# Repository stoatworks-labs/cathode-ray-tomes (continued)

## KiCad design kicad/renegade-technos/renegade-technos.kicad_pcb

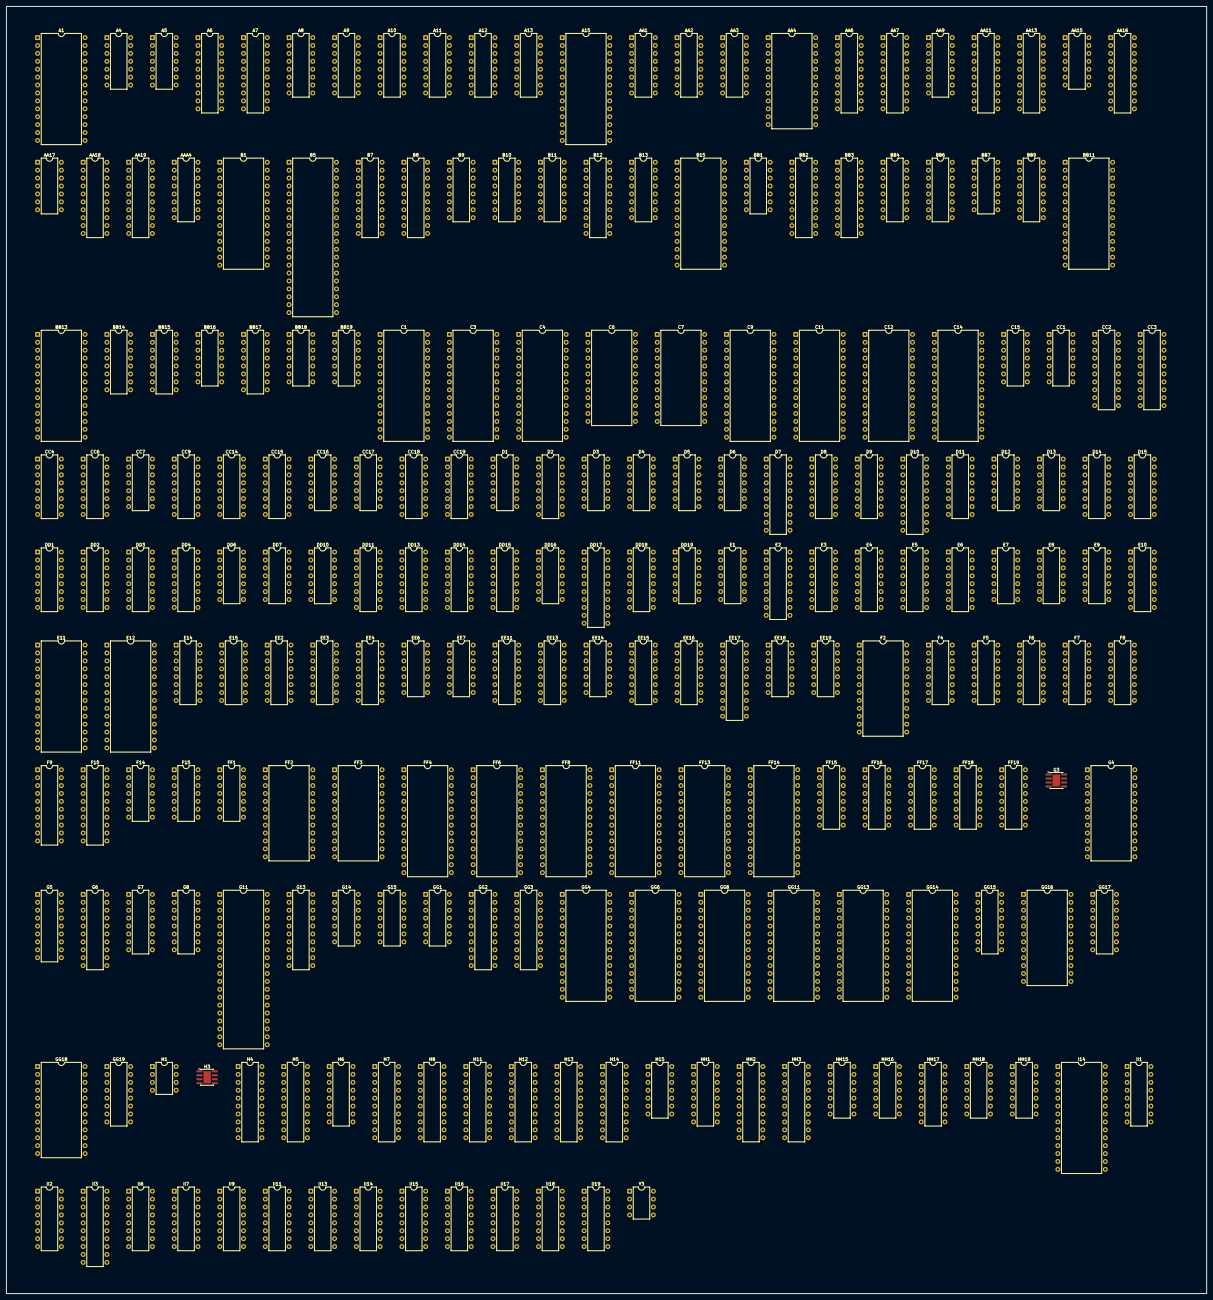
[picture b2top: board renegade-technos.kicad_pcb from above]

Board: 2 copper layers, 385.3 x 413.2 mm, 216 parts (0 on the bottom side), 819 nets, no tracks yet.

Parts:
A1, A15: 27256; DIP-28_W15.24mm
A4: 74LS08; DIP-14_W7.62mm
A5: 74LS00; DIP-14_W7.62mm
A6: 74LS374; DIP-20_W7.62mm
A7: 74LS273; DIP-20_W7.62mm
A8, A9: 74LS174; DIP-16_W7.62mm
A10, A11, A12: 74LS283; DIP-16_W7.62mm
A13: 74LS157; DIP-16_W7.62mm
AA1, AA2, AA3, AA9: 74LS157; DIP-16_W7.62mm
AA4: RAM_2016; DIP-24_W15.24mm
AA6, AA13, AA16: 74LS273; DIP-20_W7.62mm
AA7, AA11: 74LS245; DIP-20_W7.62mm
AA15: 74LS04; DIP-14_W7.62mm
AA17: 74LS86; DIP-14_W7.62mm
AA18, AA19: DIP-20_W7.62mm
AAA4: 74LS138; DIP-16_W7.62mm
B1: HM65256B_SERIES; DIP-28_W15.24mm
B5: MC68A09; DIP-40_W15.24mm
B7, B8: 74LS245; DIP-20_W7.62mm
B9, B10, B11: 74LS157; DIP-16_W7.62mm
B12: 74LS273; DIP-20_W7.62mm
B13: 74LS194; DIP-16_W7.62mm
B15: 27256; DIP-28_W15.24mm
BB1: 74LS10; DIP-14_W7.62mm
BB2, BB3: DIP-20_W7.62mm
BB4, BB6: DIP-16_W7.62mm
BB7: 74LS20; DIP-14_W7.62mm
BB9, BB14: 74LS157; DIP-16_W7.62mm
BB11: HM65256B_SERIES; DIP-28_W15.24mm
BB13: 27256; DIP-28_W15.24mm
BB15, BB17: 74LS163; DIP-16_W7.62mm
BB16, BB18, BB19: 74LS86; DIP-14_W7.62mm
C1, C3, C4, C9, C11, C12, C14: 27256; DIP-28_W15.24mm
C6, C7: RAM_2016; DIP-24_W15.24mm
C15: 74LS04; DIP-14_W7.62mm
CC1: 74LS74; DIP-14_W7.62mm
CC2, CC3: DIP-20_W7.62mm
CC4, CC6, CC14: DIP-16_W7.62mm
CC7: 74LS32; DIP-14_W7.62mm
CC9: 74LS157; DIP-16_W7.62mm
CC15: 74LS163; DIP-16_W7.62mm
CC16: 74LS00; DIP-14_W7.62mm
CC17: 74LS04; DIP-14_W7.62mm
CC18, CC19: 74LS161; DIP-16_W7.62mm
D1, D3: 74LS393; DIP-14_W7.62mm
D2, D15: 74LS157; DIP-16_W7.62mm
D4: 74LS74; DIP-14_W7.62mm
D5: 74LS27; DIP-14_W7.62mm
D6: 74LS04; DIP-14_W7.62mm
D7, D10: 74LS273; DIP-20_W7.62mm
D8, D9: 74LS174; DIP-16_W7.62mm
D11: 74LS139; DIP-16_W7.62mm
D12: 74LS10; DIP-14_W7.62mm
D13: 74LS86; DIP-14_W7.62mm
D14: 74LS194; DIP-16_W7.62mm
DD1: 74LS138; DIP-16_W7.62mm
DD2, DD3: 74LS157; DIP-16_W7.62mm
DD4: 74LS161; DIP-16_W7.62mm
DD6, DD7, DD16: 74LS74; DIP-14_W7.62mm
DD10: 74LS86; DIP-14_W7.62mm
DD11, DD13: 74LS174; DIP-16_W7.62mm
DD14, DD15: DIP-16_W7.62mm
DD17: DIP-20_W7.62mm
DD18: 74LS112; DIP-16_W7.62mm
DD19: 74LS30; DIP-14_W7.62mm
E1, E8: 74LS04; DIP-14_W7.62mm
E2: OKI-M5205; DIP-18_W7.62mm
E3: 74LS174; DIP-16_W7.62mm
E4, E5, E6: 74LS153; DIP-16_W7.62mm
E7: 74LS32; DIP-14_W7.62mm
E9: 74LS20; DIP-14_W7.62mm
E10: 74LS138; DIP-16_W7.62mm
E11, E12: 27256; DIP-28_W15.24mm
E14: 74LS194; DIP-16_W7.62mm
E15: 74LS157; DIP-16_W7.62mm
EE2, EE3, EE15, EE16: 74LS157; DIP-16_W7.62mm
EE4: 74LS161; DIP-16_W7.62mm
EE6: 74LS74; DIP-14_W7.62mm
EE7: 74LS02; DIP-14_W7.62mm
EE11: 74LS138; DIP-16_W7.62mm
EE13: 74LS139; DIP-16_W7.62mm
EE14: 74LS27; DIP-14_W7.62mm
EE17: DIP-20_W7.62mm
EE18: 74LS00; DIP-14_W7.62mm
EE19: 74LS04; DIP-14_W7.62mm
F2: YM3812-3526; DIP-24_W15.24mm
F4, F5, F6, F7: 74LS157; DIP-16_W7.62mm
F8: 74LS174; DIP-16_W7.62mm
F9, F10: 74LS244; DIP-20_W7.62mm
F14: 74LS08; DIP-14_W7.62mm
F15: 74LS14; DIP-14_W7.62mm
FF1: 74LS74; DIP-14_W7.62mm
FF2, FF3: DIP-24_W15.24mm
FF4, FF6, FF8, FF11, FF13, FF14: 27256; DIP-28_W15.24mm
FF15, FF19: 74LS257; DIP-16_W7.62mm
FF16, FF18: 74LS174; DIP-16_W7.62mm
FF17: 74LS157; DIP-16_W7.62mm
G3: L8410-LM358N; SOIC-8-1EP_3.9x4.9mm_P1.27mm_EP2.41x3.81mm
G4: RAM_2016; DIP-24_W15.24mm
G5: NEC_UPD2114; DIP-18_W7.62mm
G6, G13: 74LS245; DIP-20_W7.62mm
G7, G8: 74LS138; DIP-16_W7.62mm
G11: UM6502; DIP-40_W15.24mm
G14, G15: 74LS74; DIP-14_W7.62mm
GG1: 74LS86; DIP-14_W7.62mm
GG2, GG3: DIP-20_W7.62mm
GG4, GG6, GG8, GG11, GG13, GG14: 27256; DIP-28_W15.24mm
GG15, GG19: 74LS257; DIP-16_W7.62mm
GG16, GG18: RAM_2016; DIP-24_W15.24mm
GG17: 74LS157; DIP-16_W7.62mm
H1: MB3730; DIP-8_W7.62mm
H3: M9012-358N; SOIC-8-1EP_3.9x4.9mm_P1.27mm_EP2.41x3.81mm
H4: 74LS245; DIP-20_W7.62mm
H5: 74LS273; DIP-20_W7.62mm
H6: 74LS174; DIP-16_W7.62mm
H7, H8, H11, H12: 74LS244; DIP-20_W7.62mm
H13, H14: 74LS374; DIP-20_W7.62mm
H15: 74LS74; DIP-14_W7.62mm
HH1: 74LS174; DIP-16_W7.62mm
HH2, HH3: DIP-20_W7.62mm
HH15, HH16, HH18, HH19: 74LS86; DIP-14_W7.62mm
HH17: 74LS157; DIP-16_W7.62mm
I14: MC68705P5S; DIP-28_W15.24mm
II1, II2: DIP-16_W7.62mm
II3: DIP-20_W7.62mm
II6, II13, II14, II17: 74LS157; DIP-16_W7.62mm
II7, II9, II11: 74LS194; DIP-16_W7.62mm
II15, II16, II18, II19: 74LS163; DIP-16_W7.62mm
Y3: YM3014; DIP-8_W7.62mm

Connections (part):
/CHPAL0: DD11.7, DD17.17
/CHPAL1: DD11.10, DD17.18
/CHPXL0: D5.4, E4.5, E4.6, EE17.2
/CHPXL1: D5.5, E4.10, E4.11, EE17.5
/CHPXL2: D5.3, E5.5, E5.6, EE17.19
/CHPXL3: DD17.16, E5.10, E5.11
/CHPXL4: DD17.19, E6.5, E6.6
/CHROM0: BB13.11, DD14.3
/CHROM1: BB13.12, DD14.4
/CHROM2: BB13.13, DD14.5
/CHROM3: BB13.15, DD14.6
/CHROM4: BB13.16, CC14.3
/CHROM5: BB13.17, CC14.4
/CN2_C17: II14.6, II14.11
/CNT_VER: DD7.12, EE18.6, EE19.9, G14.3, H8.8
/COUNTER_S0: CC14.9, D15.4, DD14.9
/COUNTER_S1: CC14.10, D15.12, DD14.10
/FLIP_B: AA17.2, AA17.5, AA17.10, AA17.13, BB16.1, BB16.5, BB16.10, BB16.13, BB18.2, BB18.5, BB18.10, BB18.13, BB19.2, BB19.5, BB19.9, BB19.13, D6.10, DD10.2, DD10.13, DD15.1, HH17.3, HH17.14
/H0: AA3.10, AA17.9, BB17.13, D12.3, D15.2, D15.13, DD1.6, EE13.2, F2.24, I14.4
/H1: AA3.6, AA17.12, BB17.12, C15.3, DD1.1, DD6.3, DD7.3, EE13.3
/H2: AA3.13, AA13.11, AA16.11, BB17.11, CC9.10, CC17.13, DD1.2, DD13.9
/H3: AA3.3, BB15.14, BB16.2, CC1.3, CC17.5, DD1.3, E2.16, EE2.14, EE3.13, GG1.1
/H4: AA2.13, BB15.13, BB16.12, CC17.9, DD16.3, EE2.2, EE3.3
/H5: AA2.3, BB15.12, BB16.4, CC16.4, EE2.5, EE3.6
/H6: AA2.6, BB15.11, BB16.9, CC16.12, CC17.11, DD2.14, DD3.13
/H7: AA2.10, CC15.14, CC17.3, DD2.2, DD3.3
/H8: AA1.3, CC1.2, CC15.13, CC16.2, CC16.13, CC17.1, DD2.5, DD3.6, DD6.2, DD10.1, DD16.4, DD18.1, DD18.13
/HBLANKING: EE6.9, EE7.9
/HF2: AA17.1, CC17.12, DD11.9
/HF3: AA16.4, BB16.3
/HF4: AA16.17, BB16.11
/HF5: AA16.3, BB16.6
/HF6: AA16.18, BB16.8
/HF7: AA16.13, AA17.6
/HF8: AA16.7, DD10.11
/HF9: AA16.14, DD10.3
/HF'0: A12.6, AA17.8
/HF'1: A12.2, AA17.11, BB13.7
/HF'2: A12.15, AA17.3, BB13.6
/HF'3: A12.11, AA16.5, BB14.3
/HF'4: A11.6, AA16.16, BB14.6
/HF'5: A11.2, AA16.2, BB14.13
/HF'6: A11.15, AA16.19, BB14.10
/HF'7: A11.11, AA16.12, BB9.10
/HF'8: A10.2, AA16.6
/HF'9: A10.6, AA16.15
/MAIN_AB0: AA3.11, B9.2, BB14.2, F4.2, F9.3, G7.1, G8.1
/MAIN_AB1: AA3.5, B9.5, BB14.14, F4.5, F9.5, G7.2, G8.2
/MAIN_AB2: AA3.14, B9.11, BB14.5, F4.11, F9.7, G7.3, G8.3
/MAIN_AB3: AA3.2, B9.14, BB14.11, F4.14, F9.9
/MAIN_AB4: AA2.14, B10.2, BB9.11, F5.2, F9.18
/MAIN_AB5: AA2.2, B10.5, BB9.5, F5.5, F9.16
/MAIN_AB6: AA2.5, B10.11, BB9.14, F5.11, F9.14
/MAIN_AB7: AA2.11, B10.14, BB9.2, F5.14, F9.12
/MAIN_AB8: AA1.2, B11.2, CC9.2, F6.2, F6.5, F6.11, F6.14, F10.3
/MAIN_AB9: B11.5, CC9.5, F10.5
/MAIN_AB10: B11.11, B11.14, CC9.11, F7.5, F7.11, F10.7
/MAIN_AB11: CC9.14, E10.1, F10.9
/MAIN_AB12: AA9.5, E10.2, F10.12
/MAIN_AB13: E10.3, F10.14
/MAIN_D0: E11.11, E12.11, G11.33, G13.11
/MAIN_D1: E11.12, E12.12, G11.32, G13.12
/MAIN_D2: E11.13, E12.13, G11.31, G13.13
/MAIN_D3: E11.15, E12.15, G11.30, G13.14
/MAIN_D4: E11.16, E12.16, G11.29, G13.15
/MAIN_D5: E11.17, E12.17, G11.28, G13.16
/MAIN_D6: E11.18, E12.18, G11.27, G13.17
/MAIN_D7: E11.19, E12.19, G11.26, G13.18
/MAIN_DB0: A6.13, A7.13, A8.14, AA7.11, AA11.11, B7.18, B8.18, G6.14, G13.9, G15.2, G15.12, H4.18, H7.18, H8.18, H11.18, H12.18, H13.3, H14.2
/MAIN_DB1: A6.14, A7.14, A8.13, AA7.14, AA11.14, B7.17, B8.17, G6.13, G13.8, H4.17, H7.3, H8.3, H11.3, H12.3, H13.18, H14.19
/MAIN_DB2: A6.17, A7.17, AA7.15, AA11.15, B7.16, B8.16, G6.12, G13.7, H4.16, H7.16, H8.16, H11.16, H12.16, H13.4, H14.5
/MAIN_DB3: A6.18, A7.18, AA7.12, AA11.12, B7.15, B8.15, G6.11, G13.6, H4.15, H7.5, H8.5, H11.5, H12.5, H13.17, H14.16
/MAIN_DB4: A6.3, A7.3, AA7.13, AA11.13, B7.14, B8.14, G13.5, H4.14, H7.14, H8.14, H11.14, H12.14, H13.7, H14.6
/MAIN_DB5: A6.4, A7.4, AA7.17, AA11.17, B7.13, B8.13, G13.4, H4.13, H7.7, H8.7, H11.7, H12.7, H13.14, H14.15
/MAIN_DB6: A6.7, A7.7, AA7.16, AA11.16, B7.12, B8.12, G13.3, H4.12, H7.12, H8.12, H11.12, H12.12, H13.8, H14.9
/MAIN_DB7: A6.8, A7.8, AA7.18, AA11.18, B7.11, B8.11, G13.2, H4.11, H7.9, H8.9, H11.9, H12.9, H13.13, H14.12
/MRAM_DB0: AA6.9, CC4.6, CC6.5
/MRAM_DB1: AA6.15, CC4.3, CC6.3
/MRAM_DB2: AA6.5, CC4.13, CC6.14
/MRAM_DB3: AA6.12, CC4.10, CC6.12
/MRAM_DB4: AA6.6, BB4.6, BB6.5
/MRAM_DB5: AA6.2, BB4.3, BB6.3
/MRAM_DB6: AA6.16, BB4.13, BB6.14
/MRAM_DB7: AA6.19, BB4.10, BB6.12
/OBJBUF0: EE17.8, GG17.4
/OBJBUF1: EE17.7, GG17.7
/OBJBUF2: EE17.13, GG17.12
/OBJBUF3: EE17.14, GG17.9
/OBJBUF4: EE17.17, FF17.12
/OBJECT_A0: FF4.10, FF6.10, FF8.10, FF11.10, FF13.10, FF14.10, GG4.10, GG6.10, GG8.10, GG11.10, GG13.10, GG14.10, II3.6
/OBJECT_A1: FF4.9, FF6.9, FF8.9, FF11.9, FF13.9, FF14.9, GG4.9, GG6.9, GG8.9, GG11.9, GG13.9, GG14.9, II3.9
/OBJECT_A2: FF4.8, FF6.8, FF8.8, FF11.8, FF13.8, FF14.8, GG4.8, GG6.8, GG8.8, GG11.8, GG13.8, GG14.8, II3.15
/OBJECT_A3: FF4.7, FF6.7, FF8.7, FF11.7, FF13.7, FF14.7, GG4.7, GG6.7, GG8.7, GG11.7, GG13.7, GG14.7, II3.12
/OBJECT_A4: FF4.6, FF6.6, FF8.6, FF11.6, FF13.6, FF14.6, GG1.6, GG4.6, GG6.6, GG8.6, GG11.6, GG13.6, GG14.6
/OBJECT_A5: FF4.5, FF6.5, FF8.5, FF11.5, FF13.5, FF14.5, GG1.11, GG4.5, GG6.5, GG8.5, GG11.5, GG13.5, GG14.5
/OBJECT_A6: FF4.4, FF6.4, FF8.4, FF11.4, FF13.4, FF14.4, GG4.4, GG6.4, GG8.4, GG11.4, GG13.4, GG14.4, HH3.9
/OBJECT_A7: FF4.3, FF6.3, FF8.3, FF11.3, FF13.3, FF14.3, GG4.3, GG6.3, GG8.3, GG11.3, GG13.3, GG14.3, HH3.5
/OBJECT_A8: FF4.25, FF6.25, FF8.25, FF11.25, FF13.25, FF14.25, GG4.25, GG6.25, GG8.25, GG11.25, GG13.25, GG14.25, HH3.2
/OBJECT_A9: FF4.24, FF6.24, FF8.24, FF11.24, FF13.24, FF14.24, GG4.24, GG6.24, GG8.24, GG11.24, GG13.24, GG14.24, HH3.12
/OBJECT_A10: FF4.21, FF6.21, FF8.21, FF11.21, FF13.21, FF14.21, GG4.21, GG6.21, GG8.21, GG11.21, GG13.21, GG14.21, HH3.19
/OBJECT_A11: FF4.23, FF6.23, FF8.23, FF11.23, FF13.23, FF14.23, GG4.23, GG6.23, GG8.23, GG11.23, GG13.23, GG14.23, HH3.15
/OBJECT_A12: FF4.2, FF6.2, FF8.2, FF11.2, FF13.2, FF14.2, GG4.2, GG6.2, GG8.2, GG11.2, GG13.2, GG14.2, HH3.16
/OBJECT_A13: FF4.26, FF6.26, FF8.26, FF11.26, FF13.26, FF14.26, GG4.26, GG6.26, GG8.26, GG11.26, GG13.26, GG14.26, HH3.6
/OBJPXL0: D5.11, E4.4, EE17.9
/OBJPXL1: D5.9, E4.12, EE17.6
/OBJPXL2: D5.10, E5.4, EE17.12
/OBJPXL3: E5.12, EE17.15
/OBJPXL4: E6.4, EE17.16
/PXLCLK: A9.9, B5.38, B12.11, B13.11, D14.11, E14.11, H5.11, H6.9
/RAM0: F4.4, G4.8, G5.5
/RAM1: F4.7, G4.7, G5.6
/RAM2: F4.9, G4.6, G5.7
/RAM3: F4.12, G4.5, G5.4
/RAM4: F5.4, G4.4, G5.3
/RAM5: F5.7, G4.3, G5.2
/RAM6: F5.9, G4.2, G5.1
/RAM7: F5.12, G4.1, G5.17
/RST_SND: F15.5, F15.8, F15.11
/R_~WB: AA7.1, AA11.1, B7.1, B8.1, E8.3, F10.16, G6.1, G7.6, G8.5, G13.1, H4.1
/SCRPXL0: E4.3, E15.7
/SCRPXL1: E4.13, E15.4
/SCRPXL2: E5.3, E15.12
/SCRPXL3: E5.13, F8.10
/SCRPXL4: E6.3, F8.12
/SCRPXL5: E6.13, F8.15
/SCR_AD0: B7.2, C6.9, D7.3
/SCR_AD1: B7.3, C6.10, D7.4
/SCR_AD2: B7.4, C6.11, D7.7
/SCR_AD3: B7.5, C6.13, D7.8
/SCR_AD4: B7.6, C6.14, D7.13
/SCR_AD5: B7.7, C6.15, D7.14
/SCR_AD6: B7.8, C6.16, D7.17
/SCR_AD7: B7.9, C6.17, D7.18
/SCR_AD8: B8.2, C7.9, D8.3
/SCR_AD9: B8.3, C7.10, D8.4
/SCR_AD10: B8.4, C7.11, D8.6
/SCR_AD11: B8.5, C7.13
/SCR_AD12: B8.6, C7.14
/SCR_AD13: B8.7, C7.15, D8.11
/SCR_AD14: B8.8, C7.16, D8.13
/SCR_AD15: B8.9, C7.17, D8.14
/SND_LATCH_WR: A6.11, D4.3, FF1.12, G8.13
/V0: BB2.1, BB18.9, CC18.14, DD2.1, DD3.1, DD7.2, DD7.11, EE2.1, EE3.1, EE6.2, EE7.5, EE7.6, GG2.1
/V1: BB18.12, CC18.13
/V2: BB18.4, CC18.12
/V3: BB18.1, CC18.11, DD19.12, G14.11
/V4: BB19.10, CC19.14, DD19.4, EE19.1
/V5: BB19.12, CC19.13, DD19.3
/V6: BB19.4, CC19.12, DD19.2
/V7: BB19.1, CC19.11, DD19.1
/VBLANKING: DD7.9, EE7.8
/VF'0: A15.10, AA19.15, B15.10, BB13.10, C9.10, C11.10, C12.10, C14.10
/VF'1: A15.9, AA19.12, B15.9, BB13.9, C9.9, C11.9, C12.9, C14.9
/VF'2: A15.8, AA19.6, B15.8, BB13.8, C9.8, C11.8, C12.8, C14.8
/VF'3: A15.7, AA19.9, B15.7, BB9.6, C9.7, C11.7, C12.7, C14.7
/VF'4: AA19.16, B10.10, BB9.13
/VF'5: AA19.19, B10.13, BB9.3
/VF'6: AA19.5, B11.3, CC9.3
/VF'7: AA19.2, B11.6, CC9.6
/YDIFF0: BB7.13, CC4.2, CC6.1
/YDIFF1: CC4.5, CC6.4
/YDIFF2: BB7.12, CC4.14, CC6.13
/YDIFF3: BB7.9, CC4.11, CC6.10
/YDIFF4: BB4.2, BB6.1
/YDIFF5: BB4.5, BB6.4, CC7.13
/YDIFF6: BB4.14, BB6.13
/YDIFF7: BB4.11, BB6.10
/characters/CODE0: AA13.9, BB13.5
/characters/CODE1: AA13.6, BB13.4
/characters/CODE2: AA13.5, BB13.3
/characters/CODE3: AA13.12, BB13.25
/characters/CODE4: AA13.15, BB13.24
/characters/CODE5: AA13.19, BB13.21
/characters/CODE6: AA13.16, BB13.23
/characters/CODE7: AA13.2, BB13.2
/characters/CODE_Q0: BB13.26, DD13.12
/characters/CODE_Q1: BB13.27, DD13.15
/characters/VRAM_A0: BB11.10, BB14.4
/characters/VRAM_A1: BB11.9, BB14.12
/characters/VRAM_A2: BB11.8, BB14.7
/characters/VRAM_A3: BB11.7, BB14.9
/characters/VRAM_A4: BB9.9, BB11.6
/characters/VRAM_A5: BB9.7, BB11.5
/characters/VRAM_A6: BB9.12, BB11.4
/characters/VRAM_A7: BB9.4, BB11.3
/characters/VRAM_A8: BB11.25, CC9.4
/characters/VRAM_A9: BB11.24, CC9.7
/characters/VRAM_A10: BB11.21, CC9.9
/characters/VRAM_A11: BB11.23, CC9.12
/characters/VRAM_A12: AA9.7, BB11.2
/characters/VRAM_D0: AA11.9, AA13.8, BB11.11, DD11.4
/characters/VRAM_D1: AA11.6, AA13.7, BB11.12, DD11.3
/characters/VRAM_D2: AA11.5, AA13.4, BB11.13
/characters/VRAM_D3: AA11.8, AA13.13, BB11.15
/characters/VRAM_D4: AA11.7, AA13.14, BB11.16
/characters/VRAM_D5: AA11.3, AA13.18, BB11.17
/characters/VRAM_D6: AA11.4, AA13.17, BB11.18, DD11.14
/characters/VRAM_D7: AA11.2, AA13.3, BB11.19, DD11.13
/characters/VRAM_Q0: DD11.5, DD13.13
/characters/VRAM_Q1: DD11.2, DD13.14
/characters/~WE_CHAR: AA9.9, BB11.27
/colmix/BLUE_CE: E8.5, F6.12
/colmix/RAM_AD0: G5.14, G6.6, H6.6
/colmix/RAM_AD1: G5.13, G6.7, H6.4
/colmix/RAM_AD2: G5.12, G6.8, H6.3
/colmix/RAM_AD3: G5.11, G6.9, H6.11
/colmix/RAM_D0: G4.9, H4.2, H5.3
/colmix/RAM_D1: G4.10, H4.3, H5.4
/colmix/RAM_D2: G4.11, H4.4, H5.7
/colmix/RAM_D3: G4.13, H4.5, H5.8
/colmix/RAM_D4: G4.14, H4.6, H5.13
/colmix/RAM_D5: G4.15, H4.7, H5.14
/colmix/RAM_D6: G4.16, H4.8, H5.17
/colmix/RAM_D7: G4.17, H4.9, H5.18
/colmix/RAM_~CS: F6.4, G4.18
/colmix/S0: D5.8, E4.14, E5.14, E6.14, F5.10
/colmix/S1: D5.6, E4.2, E5.2, E6.2, F5.13
/colmix/TLS_MTPX0: E4.7, F4.3
/colmix/TLS_MTPX1: E4.9, F4.6
/colmix/TLS_MTPX2: E5.7, F4.13
/colmix/TLS_MTPX3: E5.9, F4.10
/colmix/TLS_MTPX4: E6.7, F5.3
/colmix/TLS_MTPX5: E6.9, F5.6
/colmix/~RG_CE: F6.7, H4.19
/main/BANK: E11.27, G15.9
/main/BANK_ROM: D11.11, E11.20
/main/BANK_SEL: G8.10, G15.11
/main/CLK_Ø2: F10.2, G11.39
/main/CLKØ2_B: D12.4, E10.6, F10.18
/main/MAIN2MCU: G8.11, H13.11, H15.10
/main/MAIN_A0: E11.10, E12.10, F9.17, G11.9
/main/MAIN_A1: E11.9, E12.9, F9.15, G11.10
/main/MAIN_A2: E11.8, E12.8, F9.13, G11.11
/main/MAIN_A3: E11.7, E12.7, F9.11, G11.12
/main/MAIN_A4: E11.6, E12.6, F9.2, G11.13
/main/MAIN_A5: E11.5, E12.5, F9.4, G11.14
/main/MAIN_A6: E11.4, E12.4, F9.6, G11.15
/main/MAIN_A7: E11.3, E12.3, F9.8, G11.16
/main/MAIN_A8: E11.25, E12.25, F10.17, G11.17
/main/MAIN_A9: E11.24, E12.24, F10.15, G11.18
/main/MAIN_A10: E11.21, E12.21, F10.13, G11.19
/main/MAIN_A11: E11.23, E12.23, F10.11, G11.20
/main/MAIN_A12: E11.2, E12.2, F10.8, G11.22
/main/MAIN_A13: E11.26, E12.26, F10.6, G11.23
/main/MAIN_A14: D11.14, E10.4, E12.27, G11.24
/main/MAIN_A15: D11.13, E8.9, E10.5, G11.25
/main/MCU_INT: H15.9, I14.8
/main/PA0: H13.2, H14.3, I14.20
/main/PA1: H13.19, H14.18, I14.21
/main/PA2: H13.5, H14.4, I14.22
/main/PA3: H13.16, H14.17, I14.23
/main/PA4: H13.6, H14.7, I14.24
/main/PA5: H13.15, H14.14, I14.25
/main/PA6: H13.9, H14.8, I14.26
/main/PA7: H13.12, H14.13, I14.27
/main/R_~W: F10.4, G11.34
/main/R_~WMAIN: D12.5, E8.4, E11.22, E12.22
/main/~IRQ: G11.4, G14.8
/main/~LATCHES: E10.7, G7.4, G7.5, G8.4
/main/~MCU2MAIN: F14.13, G7.11, H14.1
/main/~MCUCLR: F14.12, G7.10, H15.13
/main/~MCU_RD: H13.1, H15.11, I14.13
/main/~MCU_WR: H14.11, H15.3, I14.14
/objects/BANK0: EE11.1, FF4.27, FF6.27, GG4.27, GG6.27, II3.16
/objects/BANK1: EE11.2, EE13.14, II3.19
/objects/BANK2: EE11.3, EE13.13, GG1.4, II3.5
/objects/CLK_H: DD4.1, EE4.1, EE18.11
/objects/CLK_H8: BB1.9, CC1.9, EE6.12
/objects/CV: AA16.1, CC19.15, DD18.2, DD18.3, EE2.11, EE3.10, EE19.13, GG1.2
/objects/H8_Q: CC1.5, CC1.12
/objects/HFLIP: FF1.9, GG1.5, GG1.12, GG15.11, GG19.11, HH1.14
/objects/HFLIP': HH1.15, II13.1, II14.1
/objects/LINE: EE6.5, EE15.1, EE16.1, FF17.1, GG17.1, HH17.1
/objects/LUTA_A0: EE2.9, FF2.8
/objects/LUTA_A1: EE2.12, FF2.7
/objects/LUTA_A2: EE2.4, FF2.6
/objects/LUTA_A3: EE2.7, FF2.5
/objects/LUTA_A4: DD2.12, FF2.4
/objects/LUTA_A5: DD2.4, FF2.3
/objects/LUTA_A6: DD2.7, FF2.2
/objects/LUTA_B0: EE3.9, FF3.8
/objects/LUTA_B1: EE3.12, FF3.7
/objects/LUTA_B2: EE3.4, FF3.6
/objects/LUTA_B3: EE3.7, FF3.5
/objects/LUTA_B4: DD3.12, FF3.4
/objects/LUTA_B5: DD3.4, FF3.3
/objects/LUTA_B6: DD3.7, FF3.2
/objects/OBJIN0: EE14.3, EE15.3, EE16.2, II13.4
/objects/OBJIN1: EE14.5, EE15.10, EE16.11, II13.7
/objects/OBJIN2: EE14.4, EE15.13, EE16.14, II13.12
/objects/OBJPAL3: HH1.3, HH2.19
/objects/OBJPAL4: HH1.4, HH2.15
/objects/PXL_CLK: AA15.3, AA15.5, BB17.14, CC2.11, CC3.11, DD6.11, EE18.10, FF16.9, FF18.9
/objects/RAM_AQ0: GG2.6, GG3.6, HH2.7, II1.2, II2.13, II16.3, II19.3
/objects/RAM_AQ1: GG2.5, GG3.5, HH2.4, HH3.4, II2.6, II16.4, II19.4
/objects/RAM_AQ2: GG2.2, GG3.2, HH2.3, HH3.3, II2.4, II16.5, II19.5
/objects/RAM_AQ3: GG2.19, GG3.19, HH2.8, HH3.13, II2.11, II16.6, II19.6
/objects/RAM_AQ4: GG2.16, GG3.16, HH2.18, HH3.18, II2.14, II15.3, II18.3
/objects/RAM_AQ5: GG2.15, GG3.15, HH2.14, HH3.14, II15.4, II18.4
/objects/RAM_AQ6: GG2.12, GG3.12, HH2.17, HH3.17, II15.5, II18.5
/objects/RAM_AQ7: GG2.9, GG3.9, HH2.13, HH3.7, II15.6, II18.6
/objects/SEL_SPRT0: FF8.27, FF11.27, FF13.27, FF14.27, GG8.27, GG11.27, GG13.27, GG14.27, II3.2, II6.1
/objects/VHQ: DD7.5, II17.1
/objects/YAUX: BB7.10, CC7.11
/objects/counters/CLK_XTAL: AA15.10, BB15.2, BB17.2, CC15.2
/objects/counters/HLC: BB15.7, BB15.10, BB17.15, CC15.7
/objects/counters/HUC: BB15.15, CC15.10, CC16.1
/objects/counters/TCV: CC18.15, CC19.7, CC19.10
/objects/counters/V8: DD18.5, DD18.11, EE18.1
/objects/counters/~OBJST3: EE13.7, EE19.5
/objects/counters/~PE: CC18.9, CC19.9, EE19.12
/objects/double_line_buffer.sch/1: EE16.7, FF19.1, GG19.1
/objects/double_line_buffer.sch/2: EE16.4, FF19.5
/objects/double_line_buffer.sch/3: EE16.12, FF19.11
/objects/double_line_buffer.sch/BLANK: EE14.6, EE15.6, EE16.5
/objects/double_line_buffer.sch/BLANK': EE15.7, FF15.1, GG15.1
/objects/double_line_buffer.sch/BUFIN0: EE15.4, FF15.5
/objects/double_line_buffer.sch/BUFIN1: EE15.9, FF15.14
/objects/double_line_buffer.sch/BUFIN2: EE15.12, FF15.11
/objects/double_line_buffer.sch/BUFIN3: FF15.2, FF19.14, HH1.2
/objects/double_line_buffer.sch/BUFIN4: GG15.2, HH1.5
/objects/double_line_buffer.sch/LINEA0: FF18.6, FF19.7, GG18.9
/objects/double_line_buffer.sch/LINEA1: FF18.4, FF19.4, GG18.10
/objects/double_line_buffer.sch/LINEA2: FF18.3, FF19.9, GG18.11
/objects/double_line_buffer.sch/LINEA3: FF18.13, FF19.12, GG18.13
/objects/double_line_buffer.sch/LINEA4: FF18.11, GG18.14, GG19.9
/objects/double_line_buffer.sch/LINEB0: FF15.7, FF16.3, GG16.9
/objects/double_line_buffer.sch/LINEB1: FF15.12, FF16.4, GG16.10
/objects/double_line_buffer.sch/LINEB2: FF15.9, FF16.6, GG16.11
/objects/double_line_buffer.sch/LINEB3: FF15.4, FF16.13, GG16.13
/objects/double_line_buffer.sch/LINEB4: FF16.11, GG15.9, GG16.14
/objects/double_line_buffer.sch/~MR_A: II17.4, II18.1, II19.1
/objects/double_line_buffer.sch/~MR_B: II15.1, II16.1, II17.12
/objects/double_line_buffer.sch/~PE_LINEA: II17.7, II18.9, II19.9
/objects/double_line_buffer.sch/~PE_LINEB: II15.9, II16.9, II17.9
/objects/obj_draw/OBJECT_D0: FF4.11, FF6.11, GG4.11, GG6.11, II6.11
/objects/obj_draw/OBJECT_D1: FF4.12, FF6.12, GG4.12, GG6.12, II6.2
/objects/obj_draw/OBJECT_D2: FF4.13, FF6.13, GG4.13, GG6.13, II6.14
/objects/obj_draw/OBJECT_D3: FF4.15, FF6.15, GG4.15, GG6.15, II6.5
/objects/obj_draw/OBJECT_D4: FF4.16, FF6.16, GG4.16, GG6.16, II6.10
/objects/obj_draw/OBJECT_D5: FF4.17, FF6.17, GG4.17, GG6.17, II6.3
/objects/obj_draw/OBJECT_D6: FF4.18, FF6.18, GG4.18, GG6.18, II6.13
/objects/obj_draw/OBJECT_D7: FF4.19, FF6.19, GG4.19, GG6.19, II6.6
/objects/obj_draw/OBJ_D0: FF8.11, FF11.11, FF13.11, FF14.11, GG8.11, GG11.11, GG13.11, GG14.11, II11.3
/objects/obj_draw/OBJ_D1: FF8.12, FF11.12, FF13.12, FF14.12, GG8.12, GG11.12, GG13.12, GG14.12, II11.4
/objects/obj_draw/OBJ_D2: FF8.13, FF11.13, FF13.13, FF14.13, GG8.13, GG11.13, GG13.13, GG14.13, II11.5
/objects/obj_draw/OBJ_D3: FF8.15, FF11.15, FF13.15, FF14.15, GG8.15, GG11.15, GG13.15, GG14.15, II11.6
/objects/obj_draw/OBJ_D4: FF8.16, FF11.16, FF13.16, FF14.16, GG8.16, GG11.16, GG13.16, GG14.16, II9.3
/objects/obj_draw/OBJ_D5: FF8.17, FF11.17, FF13.17, FF14.17, GG8.17, GG11.17, GG13.17, GG14.17, II9.4
/objects/obj_draw/OBJ_D6: FF8.18, FF11.18, FF13.18, FF14.18, GG8.18, GG11.18, GG13.18, GG14.18, II9.5
/objects/obj_draw/OBJ_D7: FF8.19, FF11.19, FF13.19, FF14.19, GG8.19, GG11.19, GG13.19, GG14.19, II9.6
/objects/obj_draw/SR0: II7.9, II9.9, II11.9, II14.9
/objects/obj_draw/SR1: II7.10, II9.10, II11.10, II14.7
/objects/obj_draw/memories_sprite.sch/~GFXA0: EE13.12, FF6.20
/objects/obj_draw/memories_sprite.sch/~GFXA1: EE11.15, FF14.20
/objects/obj_draw/memories_sprite.sch/~GFXA2: EE11.14, GG14.20
/objects/obj_draw/memories_sprite.sch/~GFXB0: EE13.11, GG6.20
/objects/obj_draw/memories_sprite.sch/~GFXB1: EE11.13, FF13.20
/objects/obj_draw/memories_sprite.sch/~GFXB2: EE11.12, GG13.20
/objects/obj_draw/memories_sprite.sch/~GFXC0: EE13.10, FF4.20
/objects/obj_draw/memories_sprite.sch/~GFXC1: EE11.11, FF11.20
/objects/obj_draw/memories_sprite.sch/~GFXC2: EE11.10, GG11.20
/objects/obj_draw/memories_sprite.sch/~GFXD0: EE13.9, GG4.20
/objects/obj_draw/memories_sprite.sch/~GFXD1: EE11.9, FF8.20
/objects/obj_draw/memories_sprite.sch/~GFXD2: EE11.7, GG8.20
/objects/obj_lut_buf/A0: AA3.9, AA4.8
/objects/obj_lut_buf/A1: AA3.7, AA4.7
/objects/obj_lut_buf/A2: AA3.12, AA4.6
/objects/obj_lut_buf/A3: AA3.4, AA4.5
/objects/obj_lut_buf/A4: AA2.12, AA4.4
/objects/obj_lut_buf/A5: AA2.4, AA4.3
/objects/obj_lut_buf/A6: AA2.7, AA4.2
/objects/obj_lut_buf/A7: AA2.9, AA4.1
/objects/obj_lut_buf/A8: AA1.4, AA4.23
/objects/obj_lut_buf/D0: AA4.9, AA6.8, AA7.9
/objects/obj_lut_buf/D1: AA4.10, AA6.14, AA7.6
/objects/obj_lut_buf/D2: AA4.11, AA6.4, AA7.5
/objects/obj_lut_buf/D3: AA4.13, AA6.13, AA7.8
/objects/obj_lut_buf/D4: AA4.14, AA6.7, AA7.7
/objects/obj_lut_buf/D5: AA4.15, AA6.3, AA7.3
/objects/obj_lut_buf/D6: AA4.16, AA6.17, AA7.4
/objects/obj_lut_buf/D7: AA4.17, AA6.18, AA7.2, CC7.12
/objects/obj_lut_buf/GFX_A0: BB2.8, BB3.8, CC4.7
/objects/obj_lut_buf/GFX_A1: BB2.7, BB3.7, CC4.4
/objects/obj_lut_buf/GFX_A2: BB2.4, BB3.4, CC4.12
/objects/obj_lut_buf/GFX_A3: BB2.3, BB3.3, CC4.9
/objects/obj_lut_buf/GFX_A4: BB2.13, BB3.13, BB4.7
/objects/obj_lut_buf/GFX_A5: BB2.14, BB3.14, BB4.4
/objects/obj_lut_buf/GFX_A6: BB2.17, BB3.17, BB4.12
/objects/obj_lut_buf/GFX_A7: BB2.18, BB3.18, BB4.9
/objects/obj_lut_buf/Q0: HH2.6, II3.3
/objects/obj_lut_buf/Q1: HH2.5, II3.17
/objects/obj_lut_buf/Q2: HH2.2, II3.18
/objects/obj_lut_buf/Q3: HH2.9, II3.4
/objects/obj_lut_buf/Q7: HH2.12, II1.1
/objects/obj_lut_buf/RAM_A0: CC2.2, FF2.9, GG2.7
/objects/obj_lut_buf/RAM_A1: CC2.5, FF2.10, GG2.4
/objects/obj_lut_buf/RAM_A2: CC2.6, FF2.11, GG2.3
/objects/obj_lut_buf/RAM_A3: CC2.9, FF2.13, GG2.18
/objects/obj_lut_buf/RAM_A4: CC2.19, FF2.14, GG2.17
/objects/obj_lut_buf/RAM_A5: CC2.16, FF2.15, GG2.14
/objects/obj_lut_buf/RAM_A6: CC2.15, FF2.16, GG2.13
/objects/obj_lut_buf/RAM_A7: CC2.12, FF2.17, GG2.8
/objects/obj_lut_buf/RAM_B0: CC3.2, FF3.9, GG3.7
/objects/obj_lut_buf/RAM_B1: CC3.5, FF3.10, GG3.4
/objects/obj_lut_buf/RAM_B2: CC3.6, FF3.11, GG3.3
/objects/obj_lut_buf/RAM_B3: CC3.9, FF3.13, GG3.18
/objects/obj_lut_buf/RAM_B4: CC3.19, FF3.14, GG3.17
/objects/obj_lut_buf/RAM_B5: CC3.16, FF3.15, GG3.14
/objects/obj_lut_buf/RAM_B6: CC3.15, FF3.16, GG3.13
/objects/obj_lut_buf/RAM_B7: CC3.12, FF3.17, GG3.8
/objects/obj_lut_buf/RAM_QM0: HH3.8, II1.4
/objects/obj_lut_buf/ROBJ_A'0: II2.12, II3.7
/objects/obj_lut_buf/ROBJ_A'1: II2.7, II3.8
/objects/obj_lut_buf/ROBJ_A'2: II2.5, II3.14
/objects/obj_lut_buf/ROBJ_A'3: II2.10, II3.13
/objects/obj_lut_buf/ROBJ_A'4: II1.3, II2.15
/objects/obj_lut_buf/VF0: AA18.14, BB18.8, CC6.6
/objects/obj_lut_buf/VF1: AA18.13, BB18.11, CC6.2
/objects/obj_lut_buf/VF2: AA18.7, BB18.6, CC6.15
/objects/obj_lut_buf/VF3: AA18.8, BB18.3, CC6.11
/objects/obj_lut_buf/VF4: AA18.17, BB6.6, BB19.8
/objects/obj_lut_buf/VF5: AA18.18, BB6.2, BB19.11
/objects/obj_lut_buf/VF6: AA18.4, BB6.15, BB19.6
/objects/obj_lut_buf/VF7: AA18.3, BB6.11, BB19.3
/objects/obj_lut_buf/~V0: BB3.1, EE7.4, GG3.1
/objects/obj_lut_buf/~WE: AA1.12, AA4.21
/objects/~B1: DD1.14, II2.9
/objects/~B3: DD1.12, HH2.11
/objects/~B5: DD1.10, FF1.11, HH3.11, II3.11
/objects/~B7: DD1.7, EE19.3, HH1.9, II17.5, II17.10
/objects/~CLK_CNTER: AA18.11, AA19.11, CC17.2, CC18.2, CC19.2
/objects/~CLK_H: CC1.11, CC17.6, EE6.3
/objects/~H8_Q: BB1.10, CC1.6
/objects/~MATCH: DD2.10, DD3.11, DD4.2, EE4.2, EE18.8
/objects/~OBJST1: BB4.1, CC4.1, EE13.5, FF1.3, GG2.11, GG3.11
/objects/~OBJST2: DD2.11, DD3.10, EE13.6
/objects/~WE_LUTA: CC2.1, DD2.9, FF2.21
/objects/~WE_LUTB: CC3.1, DD3.9, FF3.21
/scroll/CARRY0: A9.15, B10.6
/scroll/CLK_SCOLM: C15.11, D13.11, F8.9
/scroll/REPAIR: A9.12, B10.3
/scroll/SCOL0: D9.2, F8.14
/scroll/SCOL1: D9.5, F8.13
/scroll/SCOL2: D9.7, F8.11
/scroll/SCR0: D7.2, D10.18
/scroll/SCR1: D7.5, D10.17
/scroll/SCR2: D7.6, D10.14
/scroll/SCR3: D7.9, D10.13
/scroll/SCR4: D7.12, D10.8
/scroll/SCR5: D7.15, D10.7
/scroll/SCR6: D7.16, D10.4
/scroll/SCR7: D7.19, D10.3
/scroll/SCR8: D8.2, D9.14
/scroll/SCR9: D8.5, D9.13
/scroll/SCR10: D8.7, D9.11
/scroll/SCR13: D8.10, D9.6
/scroll/SCR14: D8.12, D9.4
/scroll/SCR15: D8.15, D9.3
/scroll/SCROM_A4: A15.6, B12.12, B15.6, C9.6, C11.6, C12.6, C14.6, D13.12
/scroll/SCROM_A5: A15.5, B15.5, C9.5, C11.5, C12.5, C14.5, C15.12
/scroll/SCROM_A6: A15.4, B15.4, C9.4, C11.4, C12.4, C14.4, D10.19
/scroll/SCROM_A7: A15.3, B15.3, C9.3, C11.3, C12.3, C14.3, D10.16
/scroll/SCROM_A8: A15.25, B15.25, C9.25, C11.25, C12.25, C14.25, D10.15
/scroll/SCROM_A9: A15.24, B15.24, C9.24, C11.24, C12.24, C14.24, D10.12
/scroll/SCROM_A10: A15.21, B15.21, C9.21, C11.21, C12.21, C14.21, D10.9
/scroll/SCROM_A11: A15.23, B15.23, C9.23, C11.23, C12.23, C14.23, D10.6
/scroll/SCROM_A12: A15.2, B15.2, C9.2, C11.2, C12.2, C14.2, D10.5
/scroll/SCROM_A13: A15.26, B15.26, C9.26, C11.26, C12.26, C14.26, D10.2
/scroll/SCROM_A14: A15.27, B15.27, D9.12, D11.2
/scroll/SCROM_A15: A13.1, C9.27, C11.27, C12.27, C14.27, D9.15
/scroll/SCRPOS0: A7.12, A12.5
/scroll/SCRPOS1: A7.15, A12.3
/scroll/SCRPOS2: A7.16, A12.14
/scroll/SCRPOS3: A7.19, A12.12
/scroll/SCRPOS4: A7.2, A11.5
/scroll/SCRPOS5: A7.5, A11.3
/scroll/SCRPOS6: A7.6, A11.14
/scroll/SCRPOS7: A7.9, A11.12
/scroll/SCRPOS8: A8.15, A10.5
/scroll/SCRPOS9: A8.12, A10.3
/scroll/SCR_A0: B9.4, C6.8, C7.8
/scroll/SCR_A1: B9.7, C6.7, C7.7
/scroll/SCR_A2: B9.9, C6.6, C7.6
/scroll/SCR_A3: B9.12, C6.5, C7.5
/scroll/SCR_A4: B10.4, C6.4, C7.4
/scroll/SCR_A5: B10.7, C6.3, C7.3
/scroll/SCR_A6: B10.9, C6.2, C7.2
/scroll/SCR_A7: B10.12, C6.1, C7.1
/scroll/SCR_A8: B11.4, C6.23, C7.23
/scroll/SCR_A9: B11.7, C6.22, C7.22
/scroll/SCR_CA0: B9.3, B12.2
/scroll/SCR_CA1: B9.10, B12.5
/scroll/SCR_CA2: B9.13, B12.6
/scroll/SCR_CA3: B9.6, B12.9
/scroll/SCR_CA5: B12.15, C15.13
/scroll/SCR_CA6: B12.16, D13.4
/scroll/SCR_CA7: B12.19, D13.1
/scroll/SD0: A11.4, B12.3
/scroll/SD1: A11.10, B12.4
/scroll/SD2: A11.1, B12.7
/scroll/SD3: A11.13, B12.8
/scroll/SD4: A12.13, B12.13
/scroll/SD5: A12.10, B12.14
/scroll/SD6: A12.1, B12.17
/scroll/SD7: A12.4, B12.18
/scroll/scrom_memories/FLIP: D13.2, D13.5, D13.13, D15.1, E15.1, G15.5
/scroll/scrom_memories/SCROM_D0: A13.2, A15.11, B15.11
/scroll/scrom_memories/SCROM_D1: A13.5, A15.12, B15.12
/scroll/scrom_memories/SCROM_D2: A13.11, A15.13, B15.13
/scroll/scrom_memories/SCROM_D3: A13.14, A15.15, B15.15
/scroll/scrom_memories/SCROM_D4: A13.3, A15.16, B15.16
/scroll/scrom_memories/SCROM_D5: A13.6, A15.17, B15.17
/scroll/scrom_memories/SCROM_D6: A13.10, A15.18, B15.18
/scroll/scrom_memories/SCROM_D7: A13.13, A15.19, B15.19
/scroll/scrom_memories/SCROM_D8: C9.11, C11.11, C12.11, C14.11, D14.3
/scroll/scrom_memories/SCROM_D9: C9.12, C11.12, C12.12, C14.12, D14.4
/scroll/scrom_memories/SCROM_D10: C9.13, C11.13, C12.13, C14.13, D14.5
/scroll/scrom_memories/SCROM_D11: C9.15, C11.15, C12.15, C14.15, D14.6
/scroll/scrom_memories/SCROM_D12: C9.16, C11.16, C12.16, C14.16, E14.3
/scroll/scrom_memories/SCROM_D13: C9.17, C11.17, C12.17, C14.17, E14.4
/scroll/scrom_memories/SCROM_D14: C9.18, C11.18, C12.18, C14.18, E14.5
/scroll/scrom_memories/SCROM_D15: C9.19, C11.19, C12.19, C14.19, E14.6
/scroll/scrom_memories/SR0-0: B13.10, D14.10, D15.7, E14.10
/scroll/scrom_memories/SR0-1: B13.9, D14.9, D15.9, E14.9
/scroll/scrom_memories/~CE_SCRB: B15.20, C15.2
/scroll/scrom_memories/~CE_SCRC: C14.20, D11.7
/scroll/scrom_memories/~CE_SCRD: C11.20, D11.5
/scroll/scrom_memories/~CE_SCRE: C12.20, D11.6
/scroll/scrom_memories/~CE_SCRF: C9.20, D11.4
/scroll/~C4: A10.7, A11.9
/scroll/~CA4: A11.7, A12.9
/scroll/~CE_SCROM: A15.20, C15.1, D9.10, D11.3
/scroll/~CE_SCR: B8.19, F7.7
/scroll/~CLK_SCOLM: C15.10, D9.9, D10.11
/scroll/~CS_SCR: B11.9, C6.18
/scroll/~RD_SND: E8.13, F7.9
/scroll/~WE_SCR: C6.21, C7.21, F7.4
/sound/A0: C1.10, C3.10, C4.10, D1.4
/sound/A1: C1.9, C3.9, C4.9, D1.5
/sound/A2: C1.8, C3.8, C4.8, D1.6, D1.13
/sound/A3: C1.7, C3.7, C4.7, D1.11
/sound/A4: C1.6, C3.6, C4.6, D1.10
/sound/A5: C1.5, C3.5, C4.5, D1.9
/sound/A6: C1.4, C3.4, C4.4, D1.8, D3.1
/sound/A7: C1.3, C3.3, C4.3, D3.3
/sound/A8: C1.25, C3.25, C4.25, D3.4
/sound/A9: C1.24, C3.24, C4.24, D3.5
/sound/A10: C1.21, C3.21, C4.21, D3.6, D3.13
/sound/A11: C1.23, C3.23, C4.23, D3.11
/sound/A12: C1.2, C3.2, C4.2, D3.10
/sound/A13: C1.26, C3.26, C4.26, E3.2
/sound/A14: C1.27, C3.27, C4.27, E3.5
/sound/A-1: D1.3, D2.1
/sound/D0: C1.11, C3.11, C4.11, D2.6
/sound/D1: C1.12, C3.12, C4.12, D2.3
/sound/D2: C1.13, C3.13, C4.13, D2.13
/sound/D3: C1.15, C3.15, C4.15, D2.10
/sound/D4: C1.16, C3.16, C4.16, D2.5
/sound/D5: C1.17, C3.17, C4.17, D2.2
/sound/D6: C1.18, C3.18, C4.18, D2.14
/sound/D7: C1.19, C3.19, C4.19, D2.11
/sound/E_SND: A5.5, B5.34
/sound/PCM_RST: D1.2, D1.12, D3.2, D3.12, D4.8, E2.15
/sound/R~W_SND: B5.32, D6.1, E7.10
/sound/S1: E2.1, E3.7
/sound/SND_A0: A1.10, B1.10, B5.8, F2.4
/sound/SND_A1: A1.9, B1.9, B5.9
/sound/SND_A2: A1.8, B1.8, B5.10
/sound/SND_A3: A1.7, B1.7, B5.11
/sound/SND_A4: A1.6, B1.6, B5.12
/sound/SND_A5: A1.5, B1.5, B5.13
/sound/SND_A6: A1.4, B1.4, B5.14
/sound/SND_A7: A1.3, B1.3, B5.15
/sound/SND_A8: A1.25, B1.25, B5.16
/sound/SND_A9: A1.24, B1.24, B5.17
/sound/SND_A10: A1.21, B1.21, B5.18
/sound/SND_A11: A1.23, AAA4.1, B1.23, B5.19
/sound/SND_A12: A1.2, AAA4.2, B5.20
/sound/SND_A13: A1.26, AAA4.3, B5.21
/sound/SND_A14: A1.27, AAA4.4, B5.22
/sound/SND_A15: AAA4.5, B5.23, D6.3
/sound/SND_D0: A1.11, A6.12, B1.11, B5.31, E3.3, F2.10
/sound/SND_D1: A1.12, A6.15, B1.12, B5.30, E3.4, F2.11
/sound/SND_D2: A1.13, A6.16, B1.13, B5.29, E3.13, F2.13
/sound/SND_D3: A1.15, A6.19, B1.15, B5.28, E3.14, F2.14
/sound/SND_D4: A1.16, A6.2, B1.16, B5.27, E3.11, F2.15
/sound/SND_D5: A1.17, A6.5, B1.17, B5.26, E3.6, F2.16
/sound/SND_D6: A1.18, A6.6, B1.18, B5.25, F2.17
/sound/SND_D7: A1.19, A6.9, B1.19, B5.24, F2.18
/sound/~CEA: C4.20, E3.10
/sound/~CEB: C1.20, E3.12
/sound/~CEC: C3.20, E3.15
/sound/~FIRQ: B5.4, F2.2
/sound/~IRQ: B5.3, D4.6
/sound/~NMI: B5.2, D4.9
/sound/~OE: A1.22, A5.4, B1.22, D6.2
/sound/~PCM_CTRL: AAA4.11, E7.9
/sound/~PCM_START: AAA4.12, D4.10
/sound/~PCM_STOP: A4.8, D4.13
/sound/~RAM_CE: A4.3, B1.20
/sound/~RESET: B5.37, F15.6
/sound/~SND_LATCH_RD: A6.1, AAA4.13, D4.1
/sound/~VCK: E1.5, E2.14
/sound/~WE: A5.6, B1.27, D6.13, F2.5
/~BLANKING: EE7.10, H5.1, H6.1
/~CLK_BLN: AA6.11, AA15.6, BB2.11, BB3.11, CC14.11, DD14.11, DD17.11, EE6.11, II7.11, II9.11, II11.11
/~FLIP_LATCH: G8.12, G15.3
/~IN0: G7.15, H7.1, H7.19
/~IN1: G7.14, H12.1, H12.19
/~IN2: G7.13, H8.1, H8.19
/~IN3: G7.12, H11.1, H11.19
/~INT_MCU: H8.6, H15.8, I14.2
/~MCU_ST: H8.13, H15.6, I14.9
/~NMI_MAIN: G11.6, G14.6
/~OBJ_CE: AA1.1, AA2.1, AA3.1, BB1.1, BB1.2, BB1.13, CC7.2, E10.11
/~PAL_CE: E7.5, E10.9, F4.1, F5.1, F6.1
/~PAL_WE: E7.6, G4.21, G5.10
/~RST_MAIN: A4.10, CC18.1, CC19.1, DD18.14, DD18.15, F2.3, F14.5, G11.40, I14.28
/~R_NMI: F14.6, G14.1
/~SCRPOS0: A7.11, G8.15
/~SCRPOS1: A8.9, G8.14
/~SCR_CE: B9.1, B10.1, B11.1, E10.10, F7.1
/~VRAM_CE: AA9.1, BB9.1, BB14.1, C15.6, CC7.4, CC7.5, CC7.10, CC9.1
/~WE_CLK: AA15.4, EE17.11, FF15.15, FF19.15, GG15.15, GG16.21, GG18.21, GG19.15, II15.2, II16.2, II18.2, II19.2
/~WE_MAIN: AA1.14, AA9.11, D12.6, E7.4, F7.2
/~Ø0_MAIN: C15.4, D7.11, D8.9, G11.37
unnamed: A1.20, D6.4
unnamed: A9.13, A10.4
unnamed: A9.14, A10.1
unnamed: A13.4, B13.3
unnamed: A13.7, B13.4
unnamed: A13.12, B13.6
unnamed: A13.9, B13.5
unnamed: AA7.19, CC7.3
unnamed: AA11.19, CC7.8
unnamed: AA15.8, AA15.11
unnamed: AA17.4, CC16.8
unnamed: AA18.2, AA19.3
unnamed: AA18.5, AA19.4
unnamed: AA18.6, AA19.7
unnamed: AA18.9, AA19.8
unnamed: AA18.12, AA19.13
unnamed: AA18.15, AA19.14
unnamed: AA18.16, AA19.17
unnamed: AA18.19, AA19.18
unnamed: A4.1, AAA4.15
unnamed: A4.2, AAA4.14
unnamed: AAA4.10, F2.7
unnamed: A4.9, AAA4.9
unnamed: B7.19, E8.12
unnamed: B11.12, E8.11
unnamed: B13.15, E15.14
unnamed: B13.12, E15.13
unnamed: BB1.6, CC7.1
unnamed: BB1.11, EE19.4
unnamed: BB1.3, BB1.4, BB1.5, BB1.12
unnamed: BB2.2, CC2.8
unnamed: BB2.5, CC2.7
unnamed: BB2.6, CC2.4
unnamed: BB2.9, CC2.3
unnamed: BB2.12, CC2.18
unnamed: BB2.15, CC2.17
unnamed: BB2.16, CC2.14
unnamed: BB2.19, CC2.13
unnamed: BB3.2, CC3.8
unnamed: BB3.5, CC3.7
unnamed: BB3.6, CC3.4
unnamed: BB3.9, CC3.3
unnamed: BB3.12, CC3.18
unnamed: BB3.15, CC3.17
unnamed: BB3.16, CC3.14
unnamed: BB3.19, CC3.13
unnamed: BB6.7, CC6.9
unnamed: C7.18, E8.10
unnamed: C15.5, E9.8
unnamed: CC7.6, CC7.9
unnamed: CC14.15, DD15.5
unnamed: CC14.14, DD15.6
unnamed: CC15.9, CC16.3
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
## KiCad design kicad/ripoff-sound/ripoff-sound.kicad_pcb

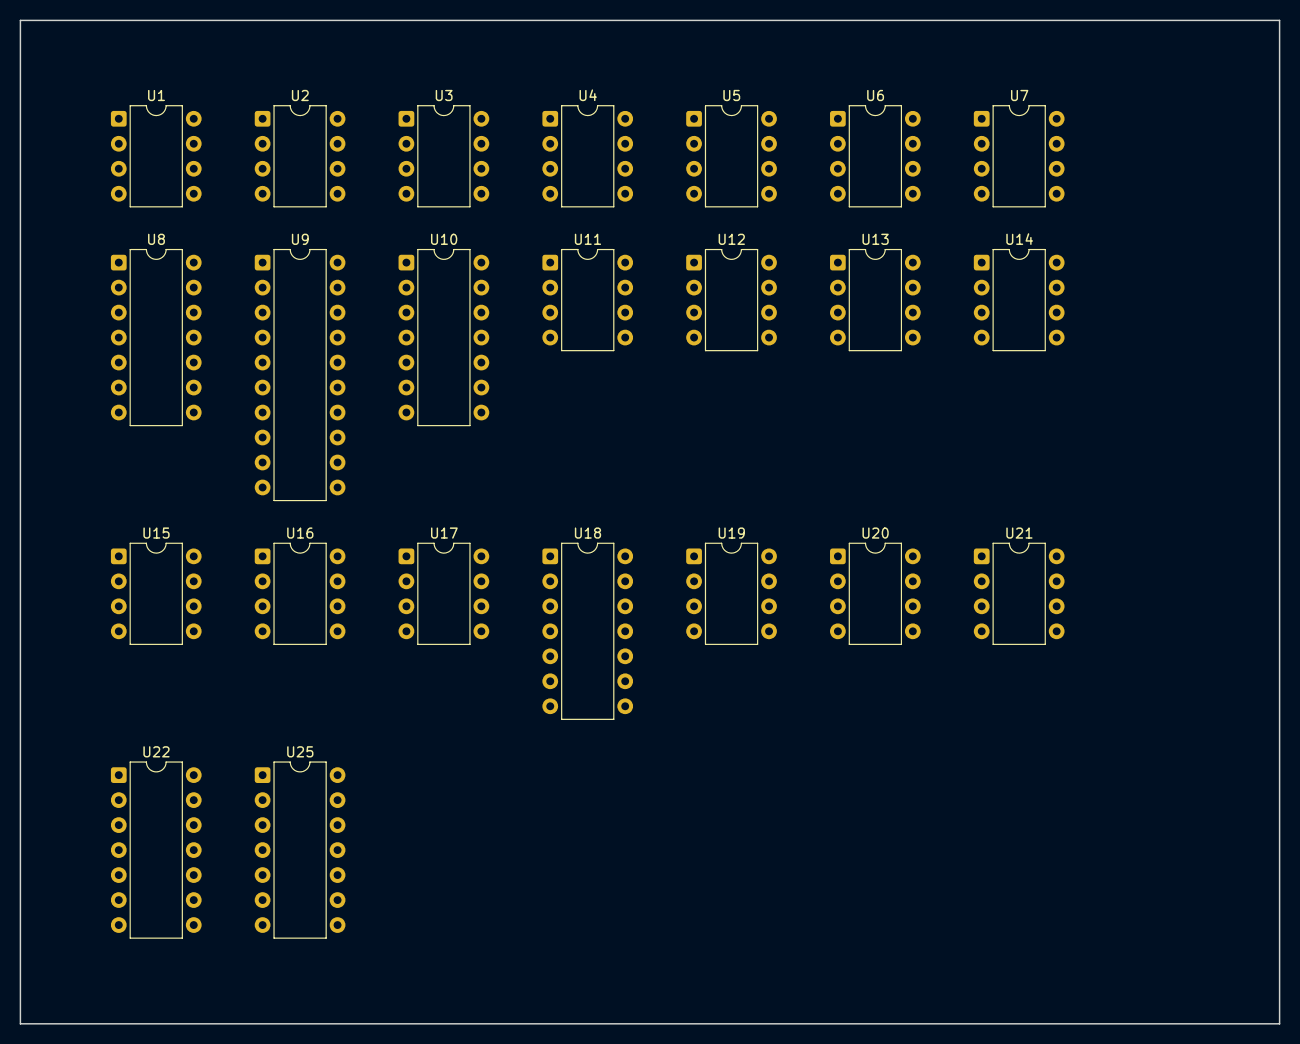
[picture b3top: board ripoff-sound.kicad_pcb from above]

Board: 2 copper layers, 128.0 x 102.0 mm, 23 parts (0 on the bottom side), 29 nets, no tracks yet.

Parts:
U1: S2688; DIP-8_W7.62mm
U2, U7, U14, U15, U16, U17, U19, U20, U21: TL081; DIP-8_W7.62mm
U3, U6, U12: CA3080; DIP-8_W7.62mm
U4, U5, U11, U13: LM555; DIP-8_W7.62mm
U8: 74LS164; DIP-14_W7.62mm
U9: 74LS377; DIP-20_W7.62mm
U10: 7406; DIP-14_W7.62mm
U18, U22: 74LS393; DIP-14_W7.62mm
U25: 7414; DIP-14_W7.62mm

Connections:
+5V: U4.4, U4.8, U5.4, U5.8, U8.14, U9.20, U10.14, U11.4, U11.8, U13.4, U13.8, U18.14, U22.14, U25.14
+15V: U1.4, U2.7, U3.7, U6.7, U7.7, U12.7, U14.7, U15.7, U16.7, U17.7, U19.7, U20.7, U21.7
-15V: U2.4, U3.4, U6.4, U7.4, U12.4, U14.4, U15.4, U16.4, U17.4, U19.4, U20.4, U21.4
GND: U1.1, U1.2, U2.3, U4.1, U5.1, U8.7, U9.1, U9.10, U10.7, U11.1, U13.1, U14.3, U18.7, U19.3, U22.7, U25.7
unnamed: U4.6, U4.7
unnamed: U5.2, U5.6
unnamed: U7.2, U7.6
unnamed: U11.2, U11.6
unnamed: U13.2, U13.6
unnamed: U3.6, U6.6, U7.3, U12.6
unnamed: U8.1, U8.9
unnamed: U8.3, U9.3
unnamed: U8.4, U9.4
unnamed: U8.5, U9.7
unnamed: U8.6, U9.8
unnamed: U8.10, U9.13
unnamed: U8.11, U9.14
unnamed: U9.2, U10.1
unnamed: U9.5, U10.3
unnamed: U9.6, U10.5
unnamed: U9.9, U22.2
unnamed: U25.6, U25.9
unnamed: U9.11, U25.8
unnamed: U8.8, U25.10
unnamed: U25.4, U25.11
unnamed: U8.2, U25.12
unnamed: U25.2, U25.13
OUT_3: U10.11, U18.2
OUT_4: U10.13, U18.12
